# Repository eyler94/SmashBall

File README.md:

# SmashBall
This is a personal project involving a ball with an internal RGB led. When you shake it, it wakes up from deep-sleep and flashes a sequence of lights, then returns to deep sleep. Mostly an excuse to learn about how to enable deep sleep with the AtTiny85 and get back into bit registry coding.

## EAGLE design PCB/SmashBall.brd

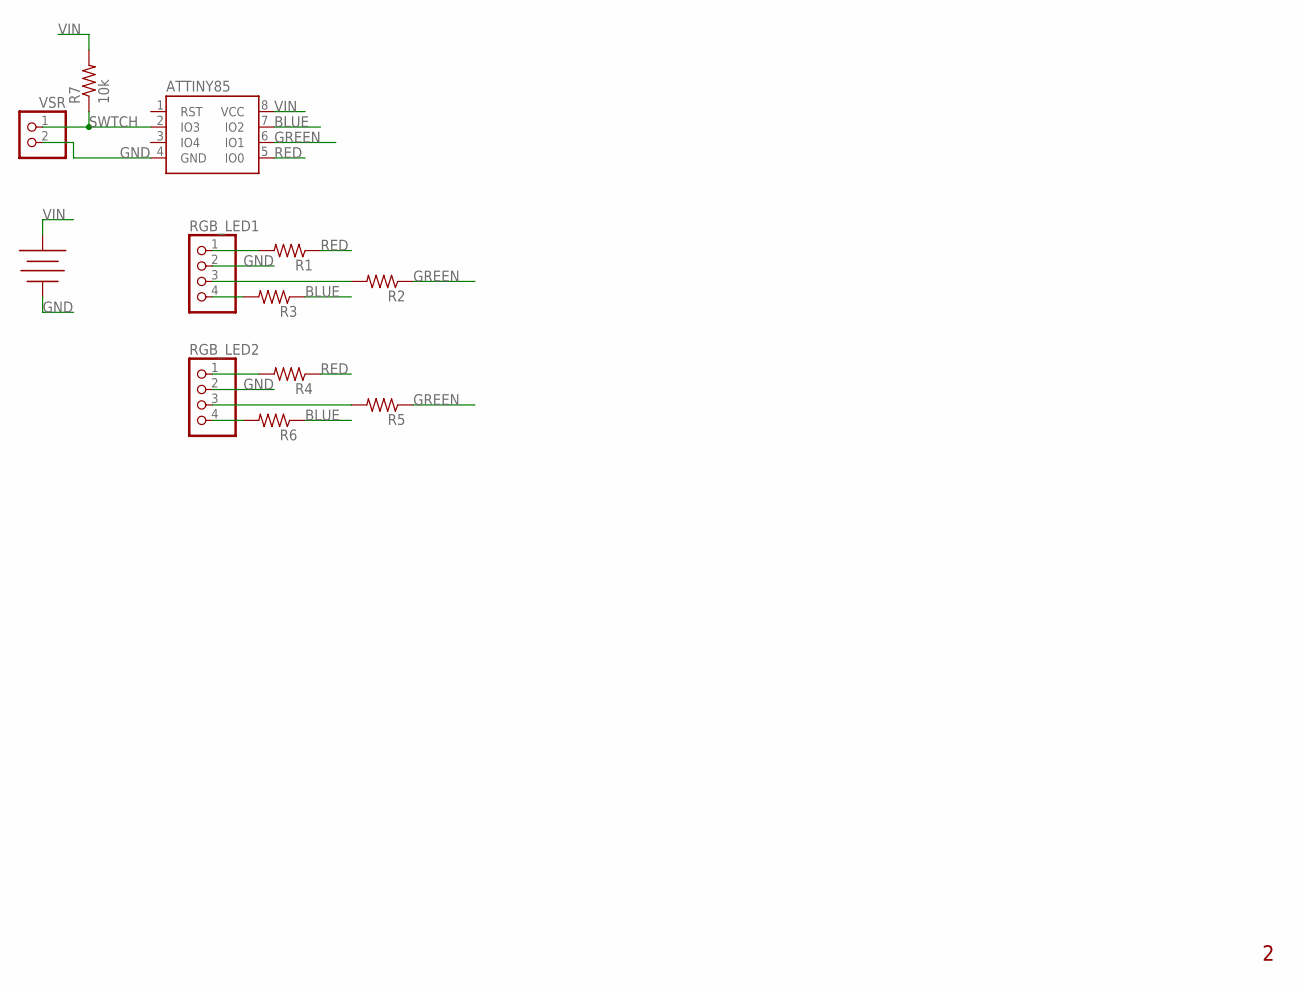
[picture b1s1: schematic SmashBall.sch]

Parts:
R1, R2, R3, R4, R5, R6: R-US_0207/2V; 0207/2V
R7: 10k; 0207/2V
RGB_LED1, RGB_LED2: PINHD-1X4; 1X04
U$1: ATTINY85; DIP762W53P254L950H370Q8B
U$2: 2032-BATTERY; 2032-BATT
VSR: PINHD-1X2; 1X02

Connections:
BLUE: R3.1, R6.1, U$1.7 (IO2)
BLUE1: R3.2, RGB_LED1.4
BLUE2: R6.2, RGB_LED2.4
GND: RGB_LED1.2, RGB_LED2.2, U$1.4 (GND), U$2.GND, VSR.2
GREEN: R2.1, R5.1, U$1.6 (IO1)
GREEN1: R2.2, RGB_LED1.3
GREEN2: R5.2, RGB_LED2.3
RED: R1.1, R4.1, U$1.5 (IO0)
RED1: R1.2, RGB_LED1.1
RED2: R4.2, RGB_LED2.1
SWTCH: R7.1, U$1.2 (IO3), VSR.1
VIN: R7.2, U$1.8 (VCC), U$2.VCC

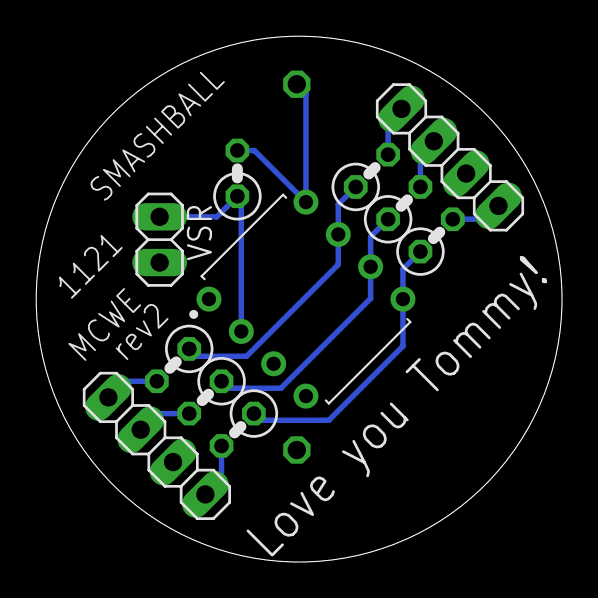
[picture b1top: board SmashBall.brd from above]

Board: 2 copper layers, 29.2 x 29.2 mm, 12 parts (1 on the bottom side), 12 nets.

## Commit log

2021-09-20 Got the code to work... I think. It's hard w/o unit tests. Big thanks to Nick Gammon and the Gadgetronicx Team.
2021-09-20 Spec'd out rev1 of the PCB. Possibly going to add 2nd RGB LED on rev 2 to help distribute light better.
2021-09-20 Generated CAM data. Now for processing!
2021-11-04 Redid the schematic and am halfway through redoing the board design.
2021-11-05 Finished layout of the board.
